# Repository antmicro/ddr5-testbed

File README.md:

# DDR5 Testbed

Copyright (c) 2022-2023 [Antmicro](https://www.antmicro.com)

## Overview

This project contains open hardware design files for an experimental test module in the mechanical form factor of SO-DIMM.
The module includes a single DDR5 RAM IC with all signals break-routed in the SO-DIMM edge connector.
The board has been designed to target Micron [MT60B2G8HB-48B:A](https://media-www.micron.com/-/media/client/global/documents/products/data-sheet/dram/ddr5/16gb_ddr5_sdram_diereva.pdf?rev=c95e4a49184145f18e105cc41e0ee643)
16Gb DRAM.
The design files were prepared in KiCad.
Please note that this board is not electrically compatible with off-the-shelf SO-DIMM DDR memory modules.
It is compatible with [this](https://github.com/antmicro/lpddr4-test-board) experimental testing platform.

### Project structure

The main project directory contains KiCad PCB project files, a LICENSE and a README.
The remaining files are stored in the following directories:

* `lib` - contains the component libraries
* `img` - contains graphics for this README
* `doc` - contains schematics in PDF form
* `assets` - contains visual assets for showcasing this design on [Open Hardware Portal](https://openhardware.antmicro.com).

## License

This project is published under the [Apache-2.0](LICENSE) license.

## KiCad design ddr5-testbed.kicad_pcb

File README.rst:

============
DDR5 testbed
============

Copyright (c) 2022 `Antmicro <https://www.antmicro.com>`_

.. figure:: img/ddr5-testbed-vis.png

Overview
--------

This repository contains open hardware design files for an experimental test module in the form of SO-DIMM.
The module includes a single DDR5 RAM IC with all signals break-routed in the SO-DIMM edge connector.
The board has been designed to target Micron `MT60B2G8HB-48B:A <https://media-www.micron.com/-/media/client/global/documents/products/data-sheet/dram/ddr5/16gb_ddr5_sdram_diereva.pdf?rev=c95e4a49184145f18e105cc41e0ee643>`_ 16Gb DRAM.
The design files were prepared in KiCad.
Please note that this board is not electrically compatible with off-the-shelf SO-DIMM DDR memory modules.
It is compatible with `this <https://github.com/antmicro/lpddr4-test-board>`_ experimental platform.

Repository structure
--------------------
The main repository directory contains KiCad PCB project files, a LICENSE and README.
The remaining files are stored in the following directories:

* ``lib`` - contains the component libraries
* ``img`` - contains graphics for this README

License
=======

`Apache-2.0 <LICENSE>`_

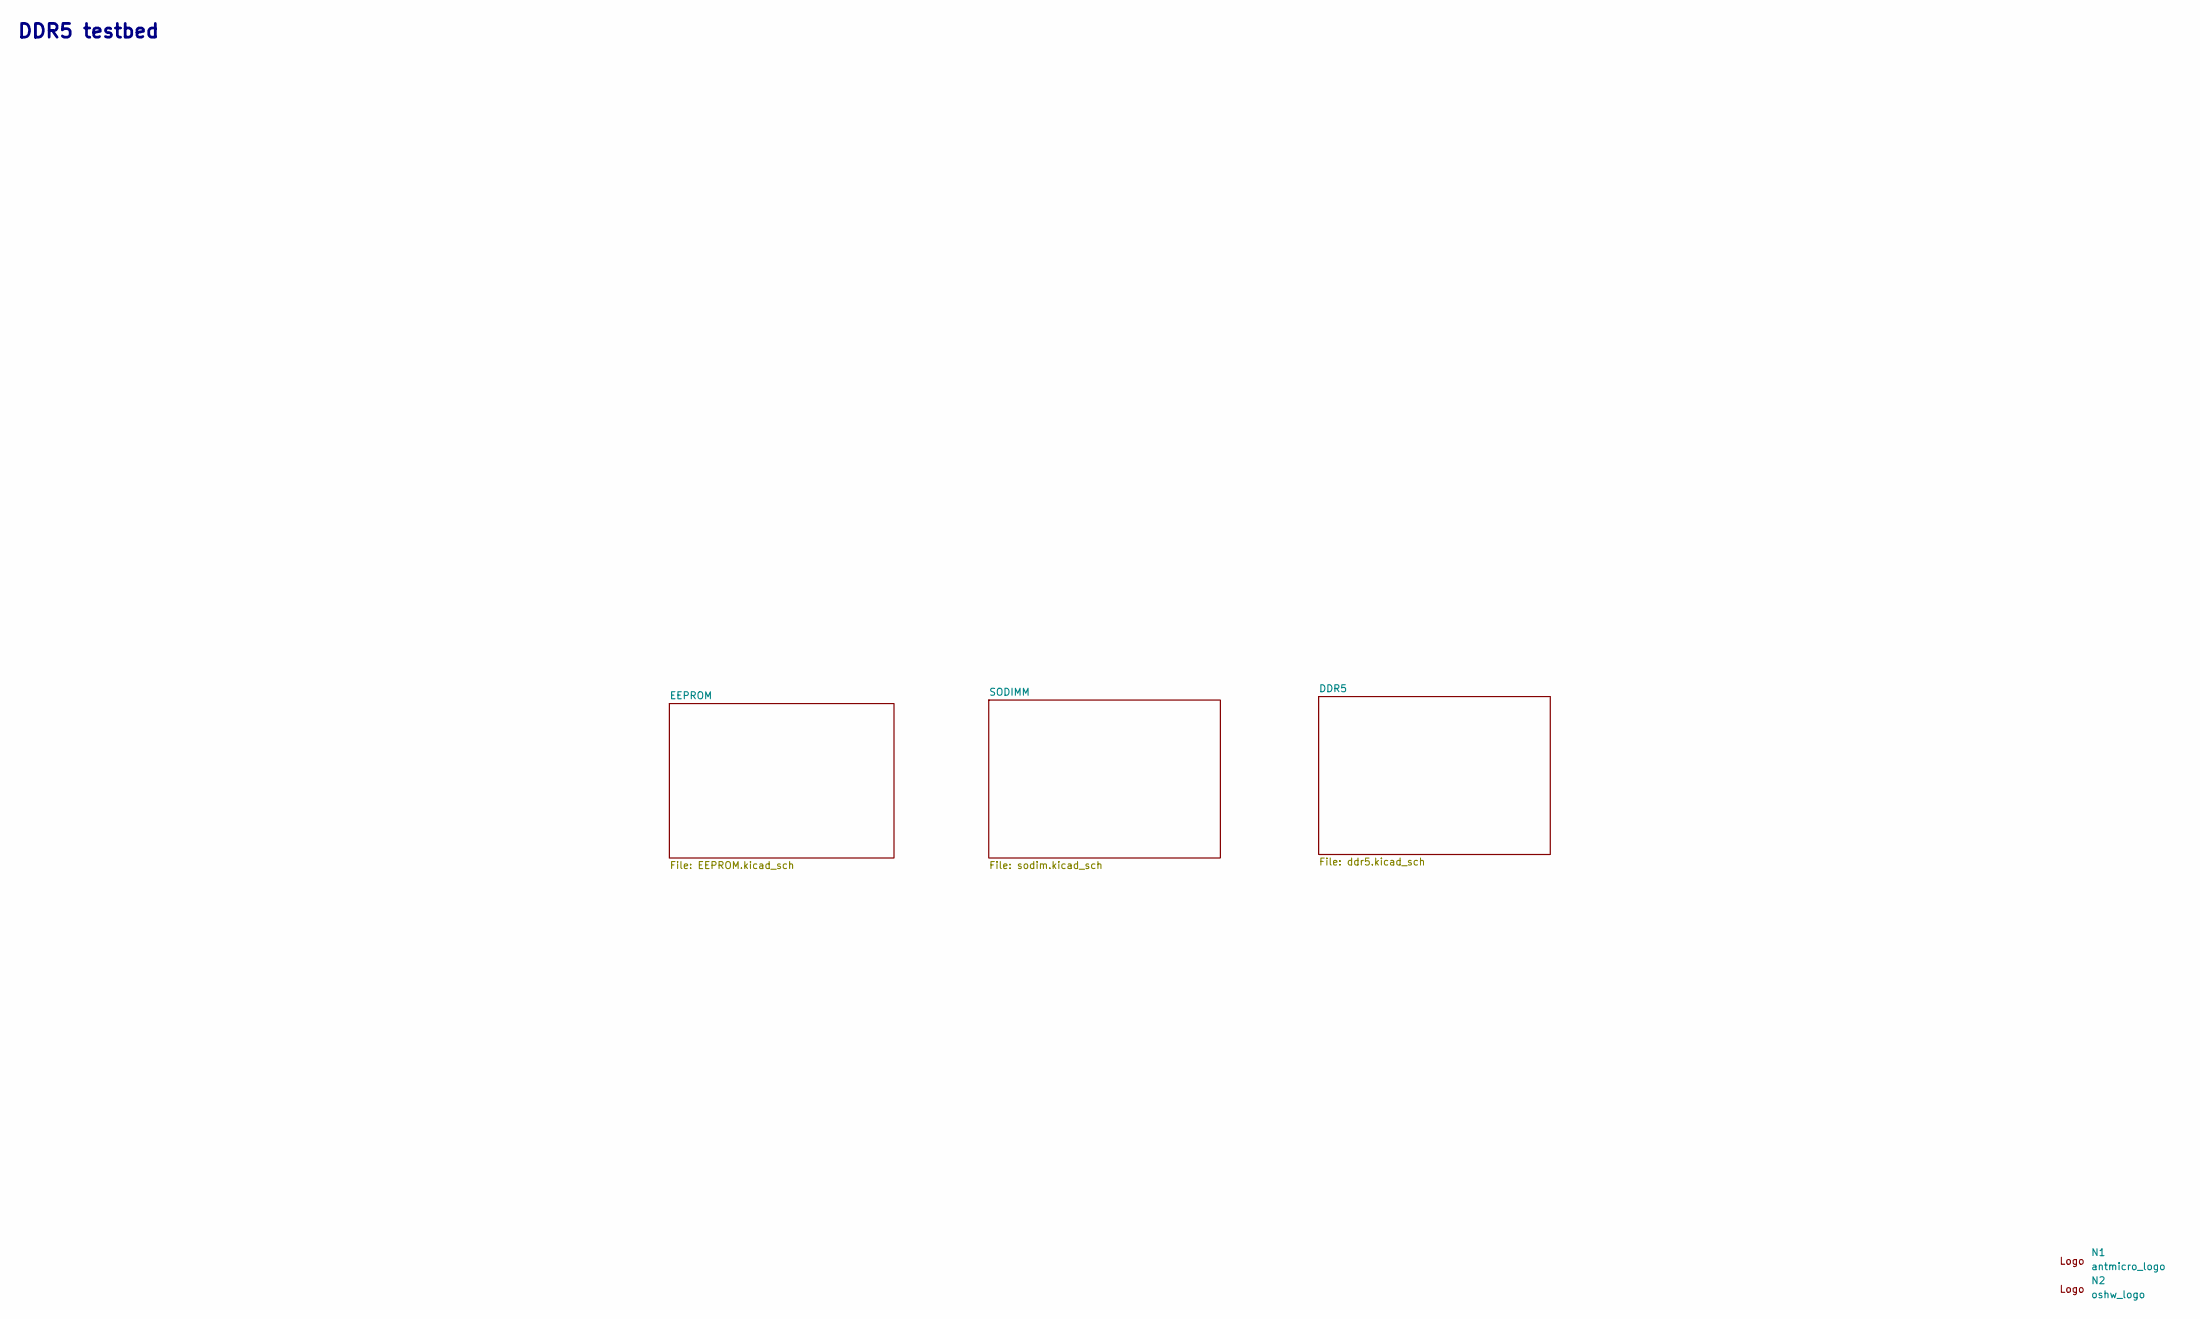
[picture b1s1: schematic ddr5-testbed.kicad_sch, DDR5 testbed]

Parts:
N1: antmicro_logo; antmicro-logo_scaled_20mm
N2: oshw_logo; oshw-logo

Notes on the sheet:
DDR5 testbed

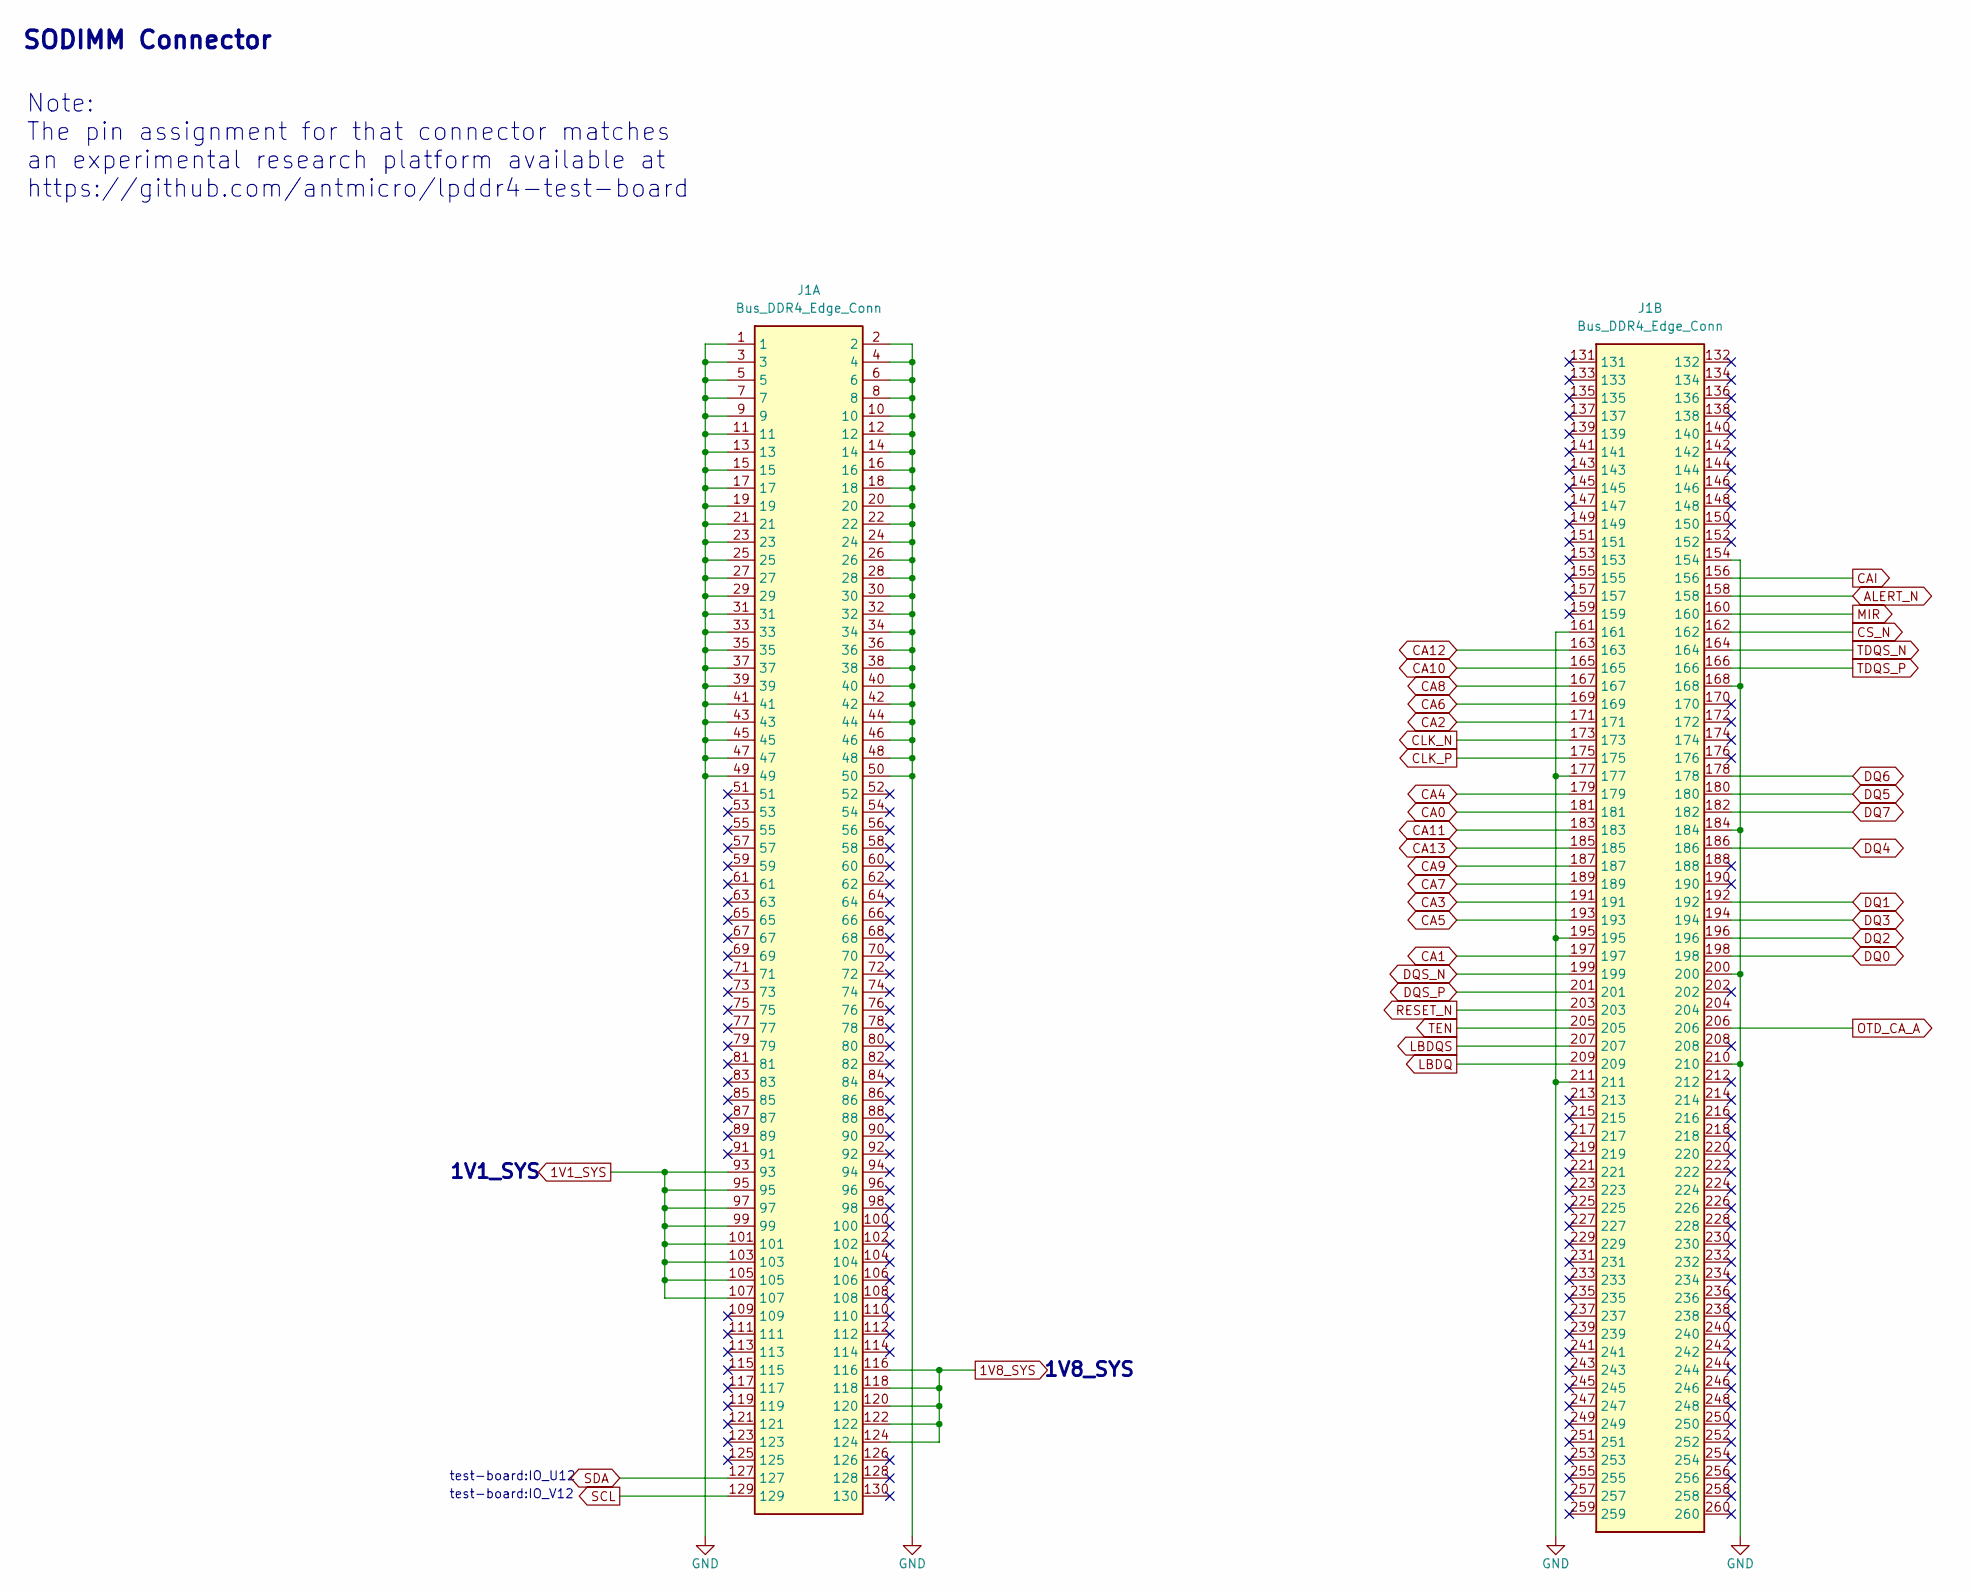
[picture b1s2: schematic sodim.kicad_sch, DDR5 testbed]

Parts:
J1: Bus_DDR4_Edge_Conn; Bus_DDR4_Conn_Edge

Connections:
1V1_SYS: J1.93, J1.95, J1.97, J1.99, J1.101, J1.103, J1.105, J1.107; also elsewhere on the board
1V8_SYS: J1.116, J1.118, J1.120, J1.122, J1.124; also elsewhere on the board
ALERT_N: J1.158; also elsewhere on the board
CA0: J1.181; also elsewhere on the board
CA1: J1.197; also elsewhere on the board
CA2: J1.171; also elsewhere on the board
CA3: J1.191; also elsewhere on the board
CA4: J1.179; also elsewhere on the board
CA5: J1.193; also elsewhere on the board
CA6: J1.169; also elsewhere on the board
CA7: J1.189; also elsewhere on the board
CA8: J1.167; also elsewhere on the board
CA9: J1.187; also elsewhere on the board
CA10: J1.165; also elsewhere on the board
CA11: J1.183; also elsewhere on the board
CA12: J1.163; also elsewhere on the board
CA13: J1.185; also elsewhere on the board
CAI: J1.156; also elsewhere on the board
CLK_N: J1.173; also elsewhere on the board
CLK_P: J1.175; also elsewhere on the board
CS_N: J1.162; also elsewhere on the board
DQ0: J1.198; also elsewhere on the board
DQ1: J1.192; also elsewhere on the board
DQ2: J1.196; also elsewhere on the board
DQ3: J1.194; also elsewhere on the board
DQ4: J1.186; also elsewhere on the board
DQ5: J1.180; also elsewhere on the board
DQ6: J1.178; also elsewhere on the board
DQ7: J1.182; also elsewhere on the board
DQS_N: J1.199; also elsewhere on the board
DQS_P: J1.201; also elsewhere on the board
GND: J1.1, J1.2, J1.3, J1.4, J1.5, J1.6, J1.7, J1.8, J1.9, J1.10, J1.11, J1.12, J1.13, J1.14, J1.15, J1.16, J1.17, J1.18, J1.19, J1.20, J1.21, J1.22, J1.23, J1.24, J1.25, J1.26, J1.27, J1.28, J1.29, J1.30, J1.31, J1.32, J1.33, J1.34, J1.35, J1.36, J1.37, J1.38, J1.39, J1.40, J1.41, J1.42, J1.43, J1.44, J1.45, J1.46, J1.47, J1.48, J1.49, J1.50, J1.154, J1.161, J1.168, J1.177, J1.184, J1.195, J1.200, J1.210, J1.211; also elsewhere on the board
LBDQ: J1.209; also elsewhere on the board
LBDQS: J1.207; also elsewhere on the board
MIR: J1.160; also elsewhere on the board
OTD_CA_A: J1.206; also elsewhere on the board
RESET_N: J1.203; also elsewhere on the board
SCL: J1.129; also elsewhere on the board
SDA: J1.127; also elsewhere on the board
TDQS_N: J1.164; also elsewhere on the board
TDQS_P: J1.166; also elsewhere on the board
TEN: J1.205; also elsewhere on the board

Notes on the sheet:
1V1_SYS
test-board:IO_V12
Note: The pin assignment for that connector matches an experimental research platform available at https://github.com/antmicro/lpddr4-test-board
SODIMM Connector
1V8_SYS
test-board:IO_U12

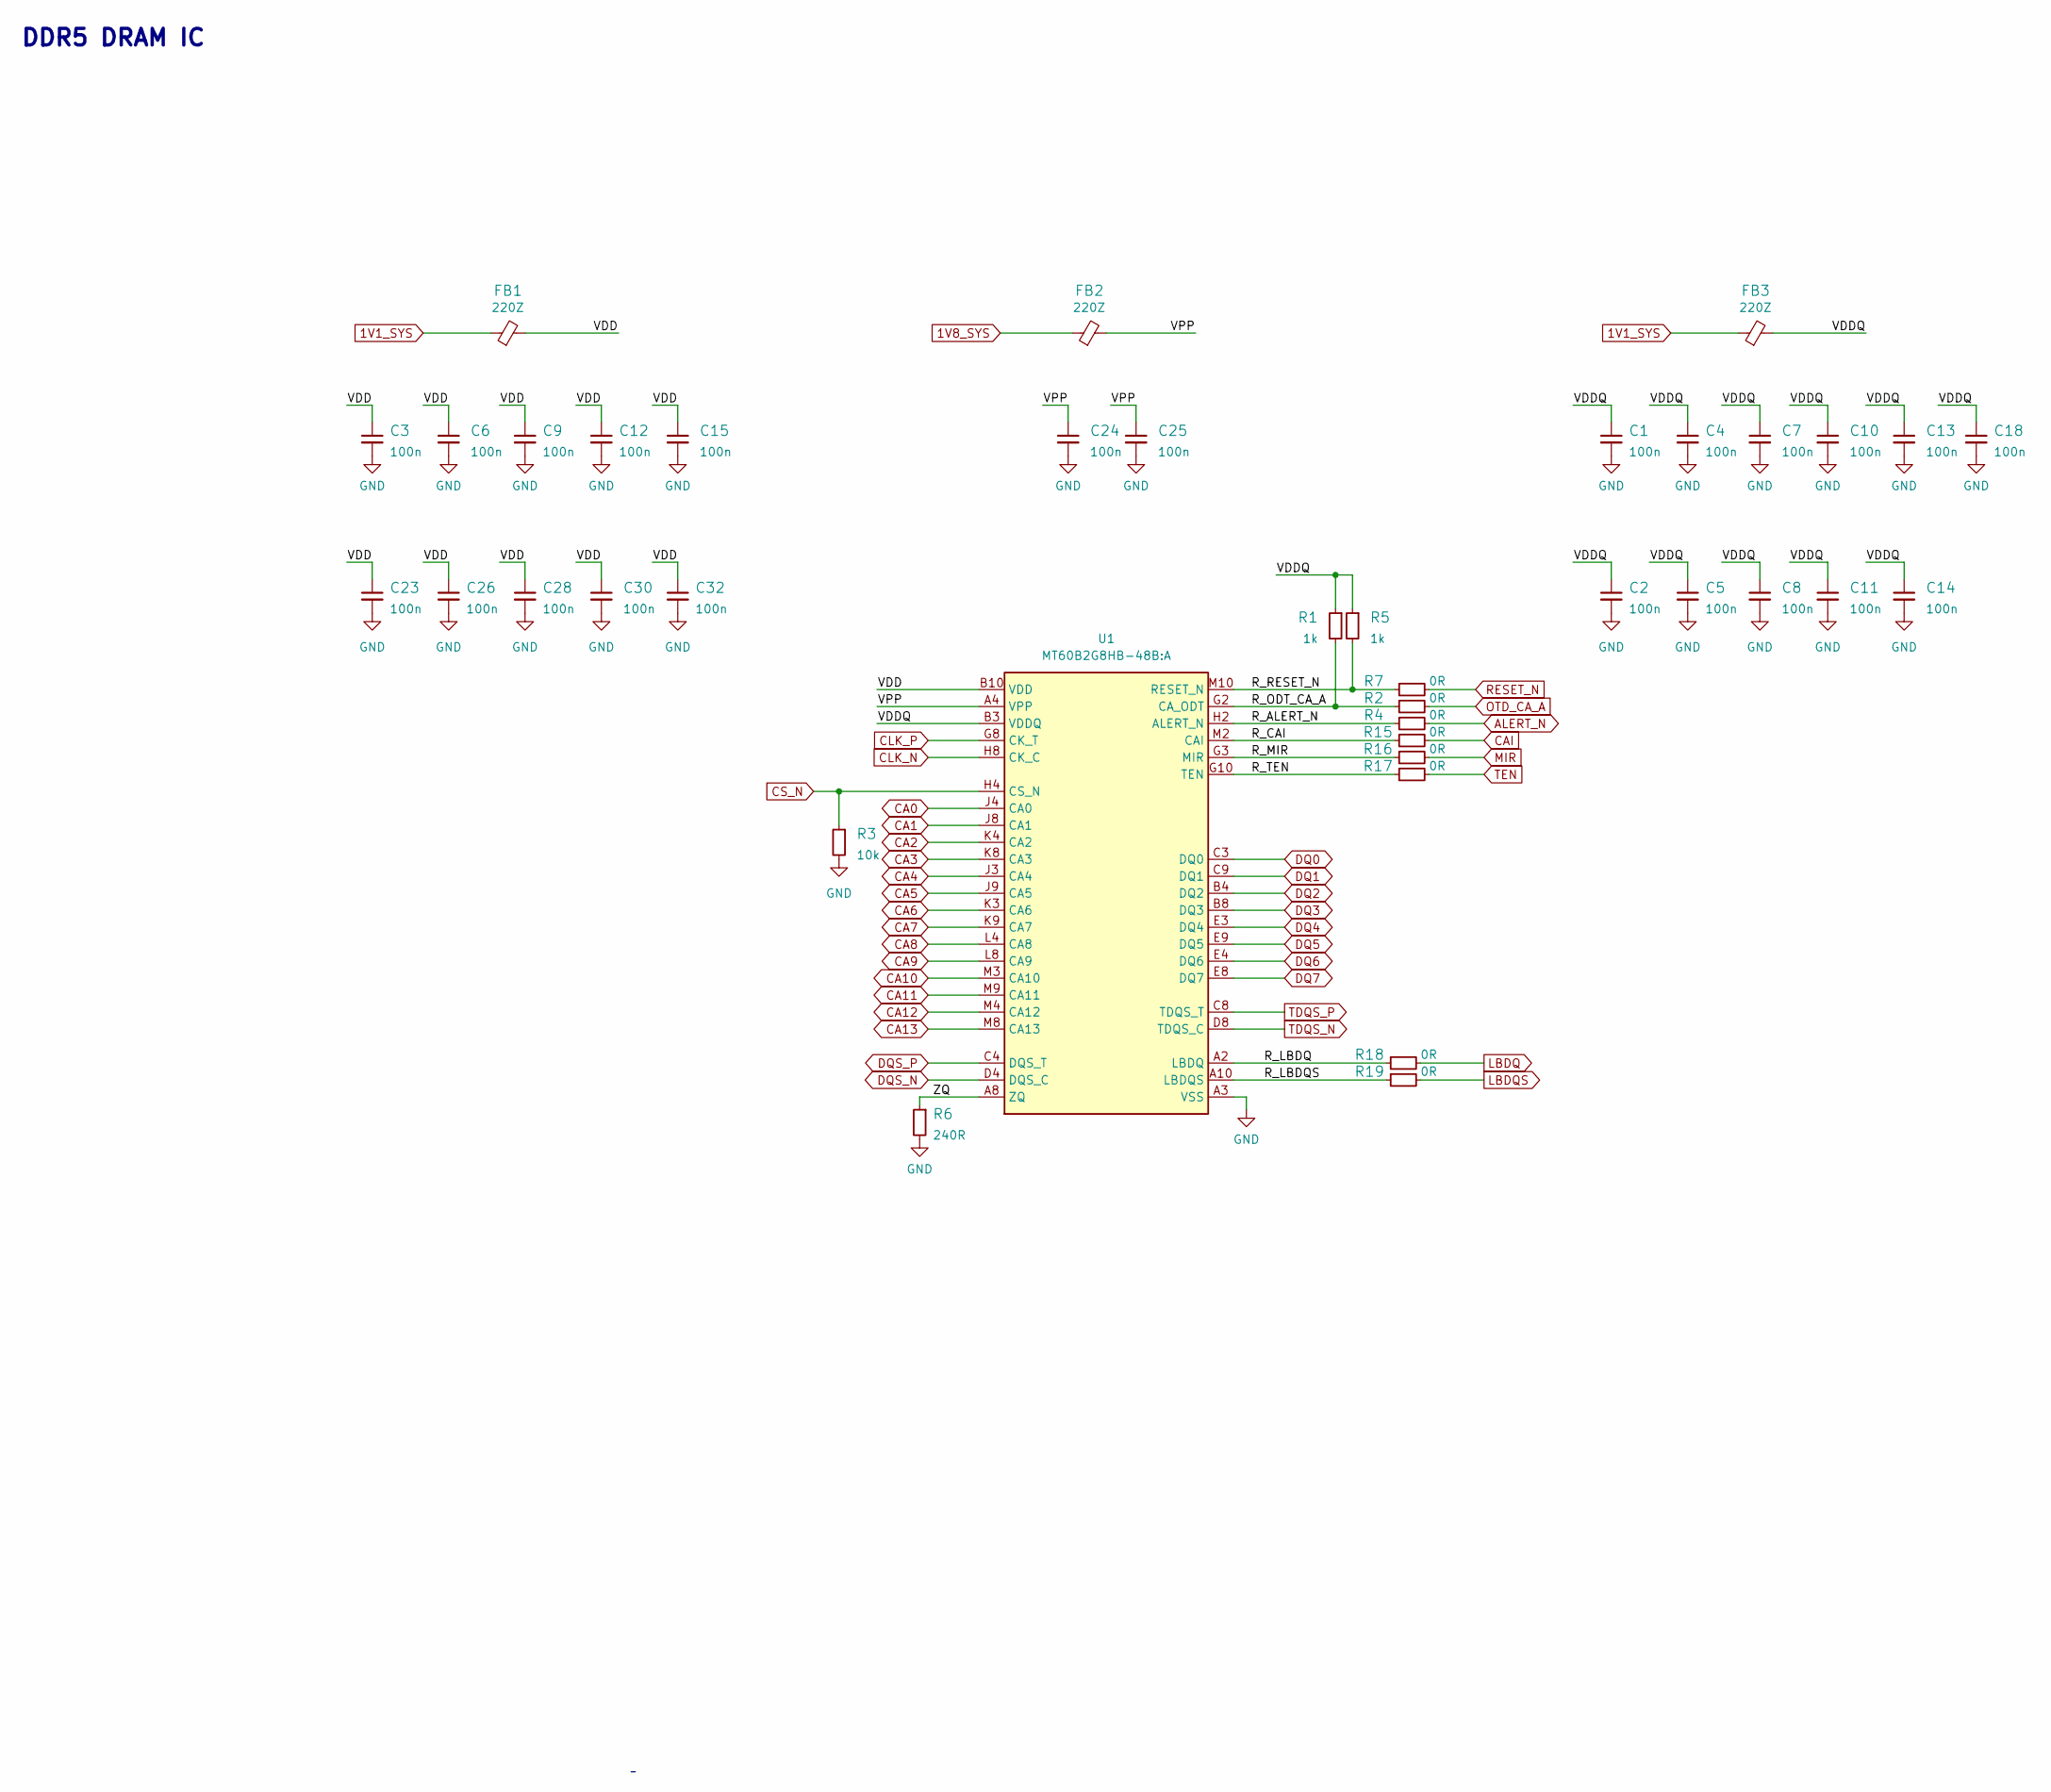
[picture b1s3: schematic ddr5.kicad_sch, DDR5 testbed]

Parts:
C1, C2, C3, C4, C5, C6, C7, C8, C9, C10, C11, C12, C13, C14, C15, C18, C23, C24, C25, C26, C28, C30, C32: C_100n_0201; C_0201; MPN CC0201KRX6S5BB104
FB1, FB2, FB3: FB_220Z_1.5A_0805; FB_0805_2012Metric; MPN 742792022
R1, R5: R_1k_0402; R_0402_1005Metric; Tolerance 1%; MPN CR0402-FX-1001GLF
R2, R4, R7, R15, R16, R17, R18, R19: R_0R_0402; R_0402_1005Metric; MPN ERJ2GE0R00X
R3: R_10k_0402; R_0402_1005Metric; Tolerance 1%; MPN CR0402-FX-1002GLF
R6: R_240R_0402; R_0402_1005Metric; Tolerance 1%; MPN CR0402-FX-2400GLF
U1: MT60B2G8HB-48B_A; BGA-82_11x9mm_Layout13x11_P0.8mm_DDR5_MO-210-AN; MPN MT60B2G8HB-48B:A

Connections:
1V1_SYS: FB1.1, FB3.1; also elsewhere on the board
1V8_SYS: FB2.1; also elsewhere on the board
/DDR5/R_ALERT_N: R4.1, U1.H2 (ALERT_N)
/DDR5/R_CAI: R15.1, U1.M2 (CAI)
/DDR5/R_LBDQ: R18.1, U1.A2 (LBDQ)
/DDR5/R_LBDQS: R19.1, U1.A10 (LBDQS)
/DDR5/R_MIR: R16.1, U1.G3 (MIR)
/DDR5/R_ODT_CA_A: R1.2, R2.1, U1.G2 (CA_ODT)
/DDR5/R_RESET_N: R5.2, R7.1, U1.M10 (RESET_N)
/DDR5/R_TEN: R17.1, U1.G10 (TEN)
/DDR5/ZQ: R6.1, U1.A8 (ZQ)
ALERT_N: R4.2; also elsewhere on the board
CA0: U1.J4 (CA0); also elsewhere on the board
CA1: U1.J8 (CA1); also elsewhere on the board
CA2: U1.K4 (CA2); also elsewhere on the board
CA3: U1.K8 (CA3); also elsewhere on the board
CA4: U1.J3 (CA4); also elsewhere on the board
CA5: U1.J9 (CA5); also elsewhere on the board
CA6: U1.K3 (CA6); also elsewhere on the board
CA7: U1.K9 (CA7); also elsewhere on the board
CA8: U1.L4 (CA8); also elsewhere on the board
CA9: U1.L8 (CA9); also elsewhere on the board
CA10: U1.M3 (CA10); also elsewhere on the board
CA11: U1.M9 (CA11); also elsewhere on the board
CA12: U1.M4 (CA12); also elsewhere on the board
CA13: U1.M8 (CA13); also elsewhere on the board
CAI: R15.2; also elsewhere on the board
CLK_N: U1.H8 (CK_C); also elsewhere on the board
CLK_P: U1.G8 (CK_T); also elsewhere on the board
CS_N: R3.1, U1.H4 (CS_N); also elsewhere on the board
DQ0: U1.C3 (DQ0); also elsewhere on the board
DQ1: U1.C9 (DQ1); also elsewhere on the board
DQ2: U1.B4 (DQ2); also elsewhere on the board
DQ3: U1.B8 (DQ3); also elsewhere on the board
DQ4: U1.E3 (DQ4); also elsewhere on the board
DQ5: U1.E9 (DQ5); also elsewhere on the board
DQ6: U1.E4 (DQ6); also elsewhere on the board
DQ7: U1.E8 (DQ7); also elsewhere on the board
DQS_N: U1.D4 (DQS_C); also elsewhere on the board
DQS_P: U1.C4 (DQS_T); also elsewhere on the board
GND: C1.2, C2.2, C3.2, C4.2, C5.2, C6.2, C7.2, C8.2, C9.2, C10.2, C11.2, C12.2, C13.2, C14.2, C15.2, C18.2, C23.2, C24.2, C25.2, C26.2, C28.2, C30.2, C32.2, R3.2, R6.2, U1.A3 (VSS), U1.A9 (VSS), U1.C2 (VSS), U1.C10 (VSS), U1.D3 (VSS), U1.D9 (VSS), U1.F2 (VSS), U1.F4 (VSS), U1.F8 (VSS), U1.F10 (VSS), U1.H3 (VSS), U1.H9 (VSS), U1.L3 (VSS), U1.L9 (VSS), U1.N3 (VSS), U1.N9 (VSS); also elsewhere on the board
LBDQ: R18.2; also elsewhere on the board
LBDQS: R19.2; also elsewhere on the board
MIR: R16.2; also elsewhere on the board
OTD_CA_A: R2.2; also elsewhere on the board
RESET_N: R7.2; also elsewhere on the board
TDQS_N: U1.D8 (TDQS_C); also elsewhere on the board
TDQS_P: U1.C8 (TDQS_T); also elsewhere on the board
TEN: R17.2; also elsewhere on the board
VDD: C3.1, C6.1, C9.1, C12.1, C15.1, C23.1, C26.1, C28.1, C30.1, C32.1, FB1.2, U1.B2 (VDD), U1.B10 (VDD), U1.E2 (VDD), U1.E10 (VDD), U1.G4 (VDD), U1.H10 (VDD), U1.K2 (VDD), U1.K10 (VDD), U1.N2 (VDD), U1.N4 (VDD), U1.N10 (VDD)
VDDQ: C1.1, C2.1, C4.1, C5.1, C7.1, C8.1, C10.1, C11.1, C13.1, C14.1, C18.1, FB3.2, R1.1, R5.1, U1.B3 (VDDQ), U1.B9 (VDDQ), U1.D2 (VDDQ), U1.D10 (VDDQ), U1.F3 (VDDQ), U1.F9 (VDDQ), U1.G9 (VDDQ), U1.J2 (VDDQ), U1.J10 (VDDQ), U1.L2 (VDDQ), U1.L10 (VDDQ)
VPP: C24.1, C25.1, FB2.2, U1.A4 (VPP), U1.N8 (VPP)

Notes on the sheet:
DDR5 DRAM IC

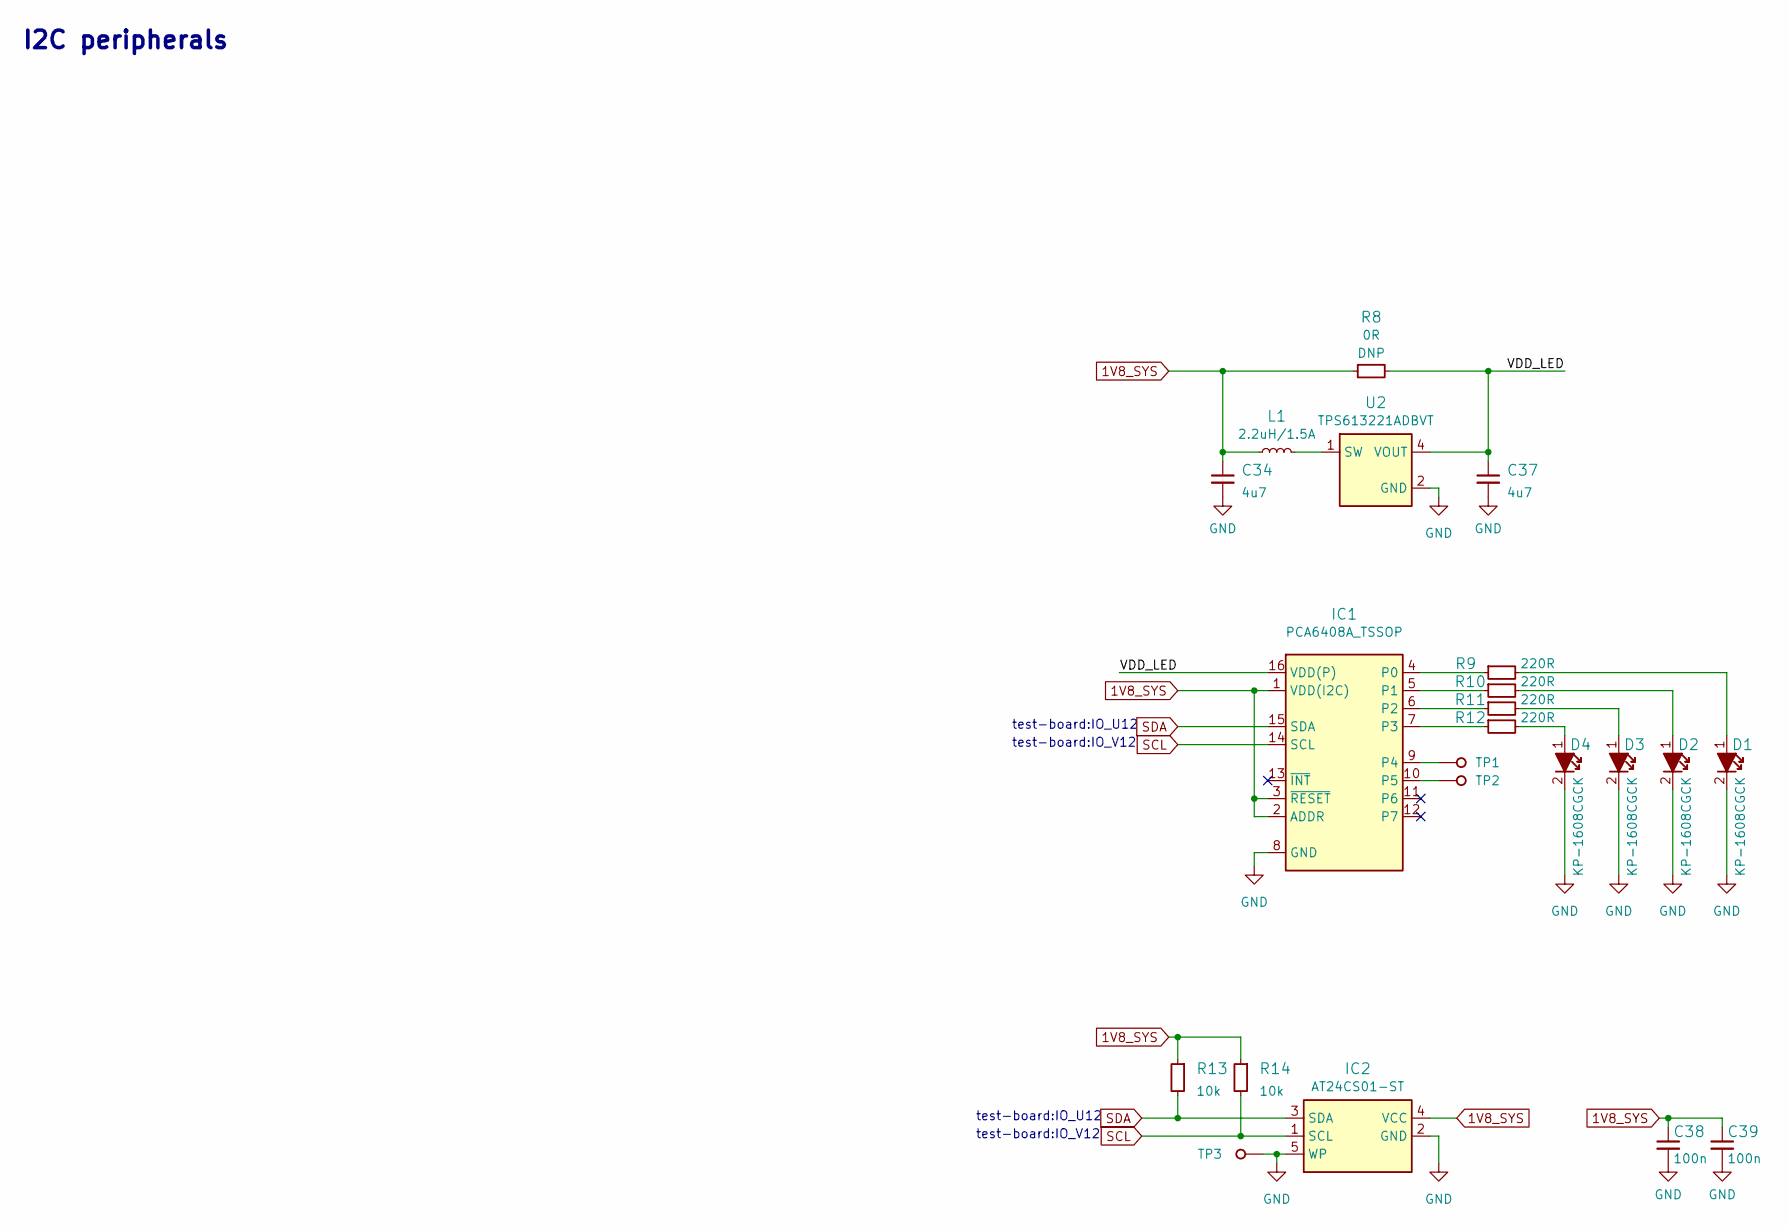
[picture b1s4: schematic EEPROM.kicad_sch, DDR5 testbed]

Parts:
C34, C37: C_4u7_0402; C_0402_1005Metric; MPN GRM155R61A475MEAAD
C38, C39: C_100n_0402; C_0402_1005Metric; Voltage 50V; MPN GRM155R61H104KE14D
D1, D2, D3, D4: LED_G_0603_KP-1608CGCK; LED_0603_1608Metric_G; MPN KP-1608CGCK
IC1: PCA6408A_TSSOP; TSSOP-16_4.4x5mm_P0.65mm; MPN PCA6408APW
IC2: AT24CS01_SOT23; SOT-23-5; MPN AT24CS01-ST
L1: L_2.2u_1.5A_0806; L_0806_2016Metric; MPN 1285AS-H-2R2M=P2
R8: R_0R_0402; R_0402_1005Metric; MPN ERJ2GE0R00X
R9, R10, R11, R12: R_220R_0402; R_0402_1005Metric; Tolerance 1%; MPN CR0402-FX-2200GLF
R13, R14: R_10k_0402; R_0402_1005Metric; Tolerance 1%; MPN CR0402-FX-1002GLF
TP1, TP2, TP3: TP_1mm_SMD; Testpoint_smd_1mm
U2: TPS613221A_SOT-23-5; SOT-23-5; MPN TPS613221ADBVT

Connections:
1V8_SYS: C34.1, C38.1, C39.1, IC1.1 (VDD(I2C)), IC1.2 (ADDR), IC1.3 (~RESET), IC2.4 (VCC), L1.1, R8.1, R13.1, R14.1; also elsewhere on the board
/EEPROM/VDD_LED: C37.1, IC1.16 (VDD(P)), R8.2, U2.4 (VOUT)
GND: C34.2, C37.2, C38.2, C39.2, D1.2, D2.2, D3.2, D4.2, IC1.8 (GND), IC2.2 (GND), IC2.5 (WP), TP3.1, U2.2 (GND); also elsewhere on the board
unnamed: D1.1, R9.2
unnamed: D2.1, R10.2
unnamed: D3.1, R11.2
unnamed: D4.1, R12.2
unnamed: IC1.4 (P0), R9.1
unnamed: IC1.5 (P1), R10.1
unnamed: IC1.6 (P2), R11.1
unnamed: IC1.7 (P3), R12.1
unnamed: IC1.9 (P4), TP1.1
unnamed: IC1.10 (P5), TP2.1
unnamed: L1.2, U2.1 (SW)
SCL: IC1.14 (SCL), IC2.1 (SCL), R14.2; also elsewhere on the board
SDA: IC1.15 (SDA), IC2.3 (SDA), R13.2; also elsewhere on the board

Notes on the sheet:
I2C peripherals
test-board:IO_U12
test-board:IO_V12

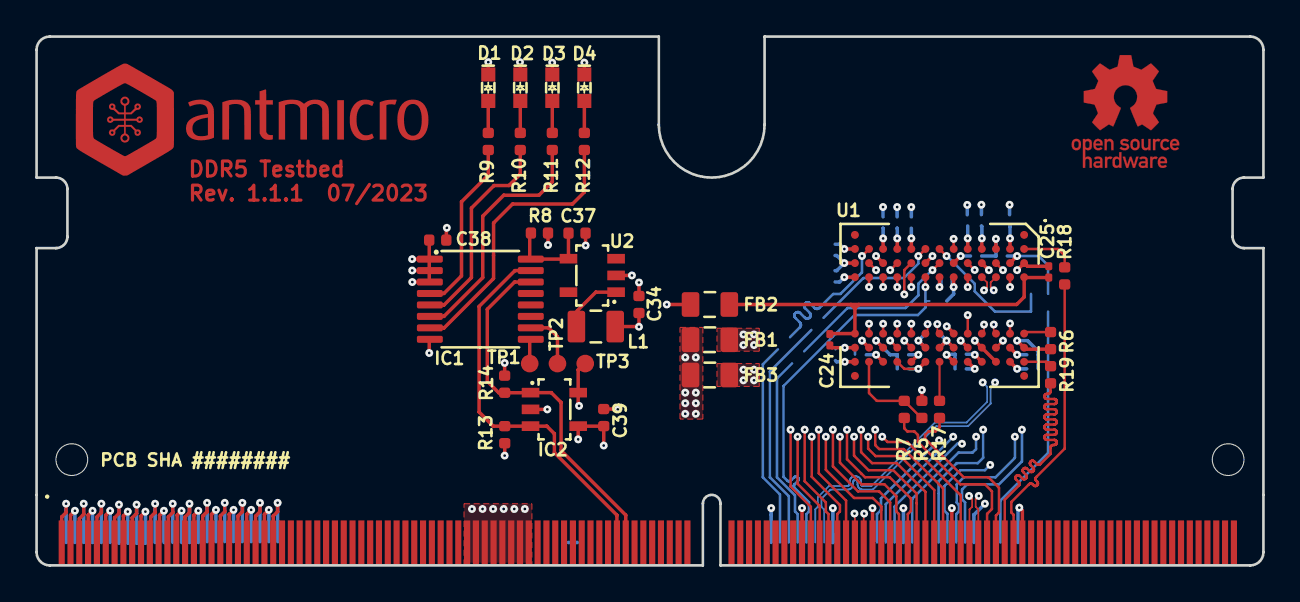
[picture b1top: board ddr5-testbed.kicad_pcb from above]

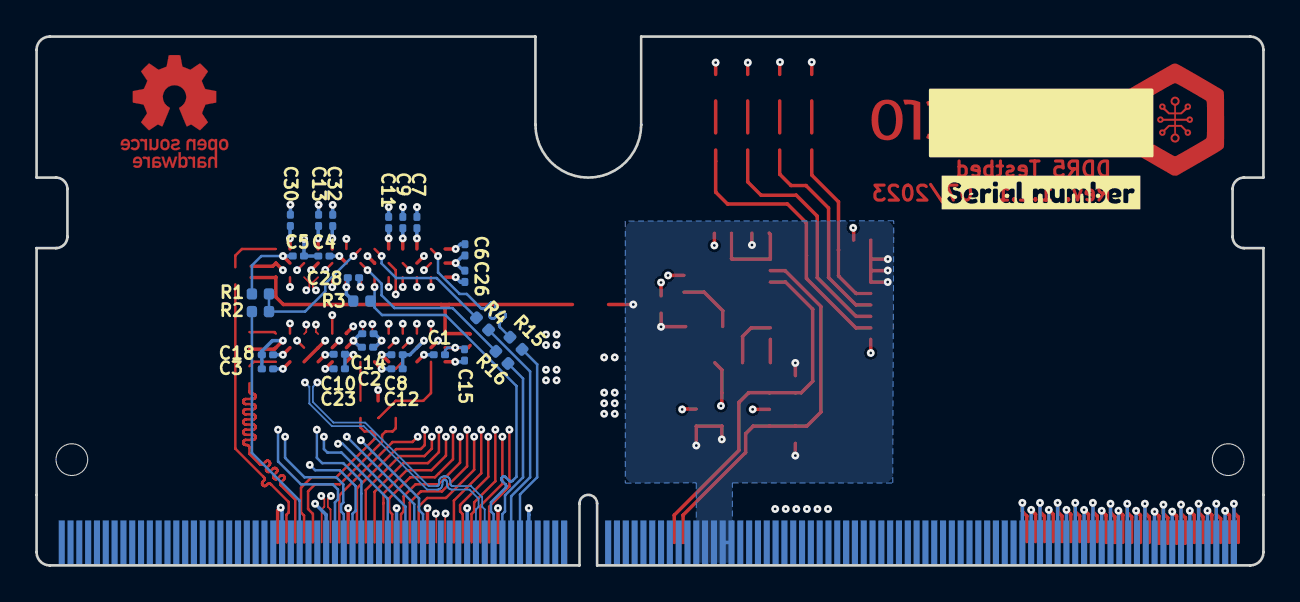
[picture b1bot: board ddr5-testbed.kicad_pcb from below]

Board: 6 copper layers, 69.6 x 30.0 mm, 65 parts (28 on the bottom side), 66 nets.

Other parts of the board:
kibuzzard-623AE55E: G***; label

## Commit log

2022-03-02 Add logtypes to schematics
2022-03-02 Add no connection flags to unused pins of IC1
2022-03-08 Reduce number of capacitors to match supply pin count, add OR resistors for control signals
2022-03-08 Geberate local libraries
2022-03-08 Update silks default values, update project name on PCB
2022-03-08 Update project name and revision on schematics
2022-03-08 Update project name on schematic
2022-03-08 Fix power labels naming scheme, remove connection from SODIM to VDDQ, add chockes to DDR5 power
2022-03-08 Add 0R resistors to LBDQ signals
2022-03-08 Update pin assignment
2022-03-08 Update net classes to match impedance, import changes from sch, add dummy 3D model of DDR5 IC
2022-03-08 Update signal assignment
2022-03-08 Remap connections
2022-03-08 Finish SODIMM connections
2022-03-08 Add signal labels to SCH
2022-03-08 Move CAI, ALERT_N, MIR and CA_ODT to other pins of SODIMM
2022-03-08 Resize schematic sheet
2022-03-08 Update SODIMM signal assignment
2022-03-08 Add board vis to sch
2022-03-08 Silks cleanup, fix date text
2022-03-08 Cleanup
2022-03-08 Add 3D Vis, fix overlapping references
2022-03-08 Change pullup resistors to 1K
2022-03-08 Tune LBDQ traces
2022-03-08 Change R6 to 1% tolerance
2022-03-08 Tune CA traces
2022-03-08 Tune DQ traces
2022-03-08 Assign schematic labels
2022-03-08 Routing
2022-03-08 Add README
2022-03-30 Update 3DVis
2022-04-07 1.0.1 production release W200350ASK113
2022-05-27 resize image
2022-06-03 Convert README to .md
2022-06-20 Add photo
2022-12-28 Migrate to KiCad 6
2022-12-28 Clear DRC
2022-12-28 Bump revision to 1.0.2
2022-12-29 Update revision on schematic sheets
2023-01-11 Corrected board stackup and thickness
2023-01-11 Added on bottom silkscreen field for serial number
2023-01-13 Added PCB SHA string
2023-01-13 Bump revision to 1.1.0
2023-03-30 Notes added by 'git notes add'
2023-06-05 Update PCB marking string
2023-10-13 Introduce component standardization
2023-10-16 Add OHP assets
2023-12-29 README: Update formatting
2023-12-29 README: list assets
2023-12-29 Add PDF schematic
2024-05-27 Bump to Kicad7
2024-05-27 Globlib
2024-05-27 Update edge connector on schematic
2024-05-27 Fix broken library references
2024-05-27 Remove lib
2024-05-27 Update footprints and symbols from library, clear DRC
2024-05-27 Fix SHA placeholder
2024-06-03 Hide edge connector designator
2024-06-03 Upload assets
2024-06-06 Update designators
2024-06-06 [#60007] Update PDF schematic
2024-06-07 Update OHP assets
